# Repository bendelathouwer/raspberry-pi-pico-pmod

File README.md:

# raspberry-pi-pico-pmod
pico breakout with pmods

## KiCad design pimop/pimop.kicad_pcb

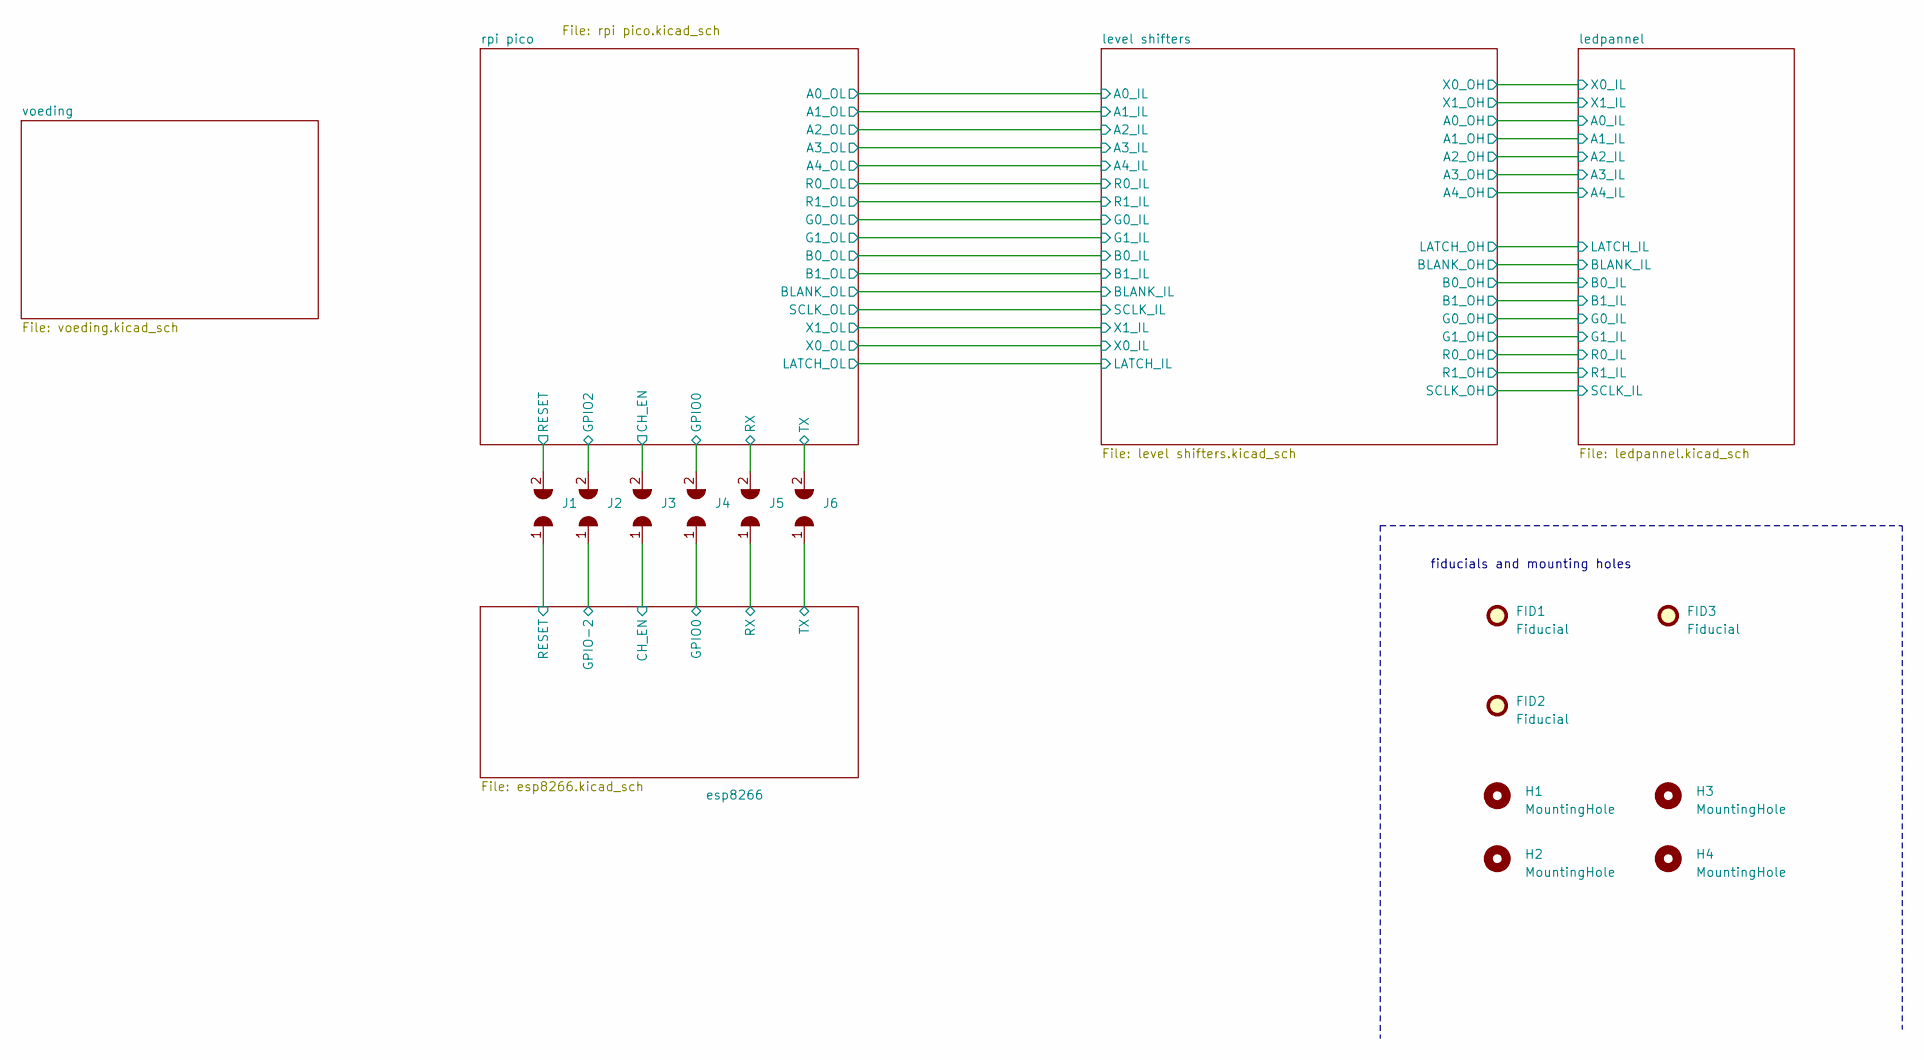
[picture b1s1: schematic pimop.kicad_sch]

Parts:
FID1, FID2, FID3: Fiducial; Fiducial_1.5mm_Mask4.5mm
H1, H2, H3, H4: MountingHole; MountingHole_2.2mm_M2_Pad
J1, J2, J3, J4, J5, J6: solderjumper_2pin; SolderJumper-2_P1.3mm_Open_Pad1.0x1.5mm

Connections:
/esp8266/CH_EN: J3.1; also elsewhere on the board
/esp8266/GPIO0: J4.1; also elsewhere on the board
/esp8266/GPIO-2: J2.1; also elsewhere on the board
/esp8266/RESET: J1.1; also elsewhere on the board
/esp8266/RX: J5.1; also elsewhere on the board
/esp8266/TX: J6.1; also elsewhere on the board
/rpi pico/GPIO16: J5.2; also elsewhere on the board
/rpi pico/GPIO17: J6.2; also elsewhere on the board
/rpi pico/GPIO18: J3.2; also elsewhere on the board
/rpi pico/GPIO19: J1.2; also elsewhere on the board
/rpi pico/GPIO20: J2.2; also elsewhere on the board
/rpi pico/GPIO21: J4.2; also elsewhere on the board

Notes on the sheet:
fiducials and mounting holes

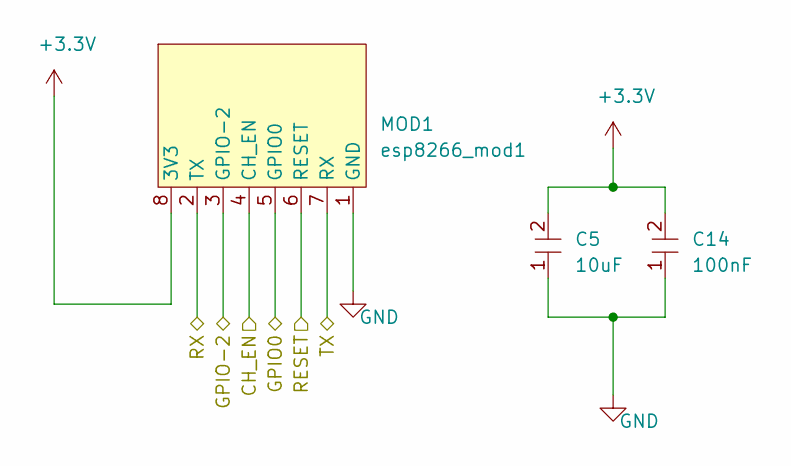
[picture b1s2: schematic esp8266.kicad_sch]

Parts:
C5: 10uF; 0603
C14: 100nF; 0603
MOD1: esp8266_mod1; esp8266mod

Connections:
+3V3: C5.2, C14.2, MOD1.8 (3V3); also elsewhere on the board
GND: C5.1, C14.1, MOD1.1 (GND); also elsewhere on the board

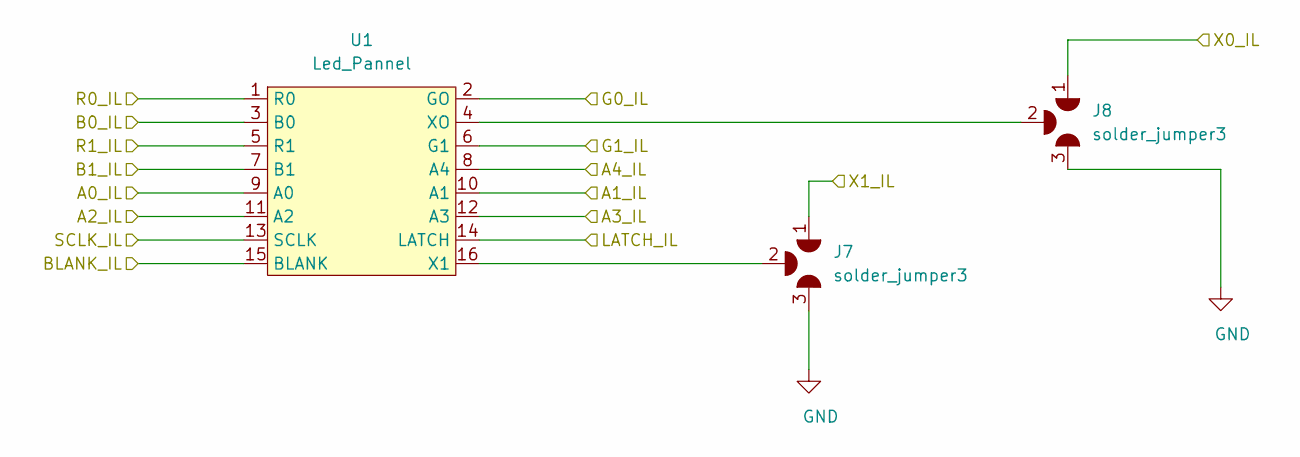
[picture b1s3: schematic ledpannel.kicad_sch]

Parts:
J7, J8: solder_jumper3; SolderJumper-3_P2.0mm_Open_TrianglePad1.0x1.5mm_NumberLabels
U1: Led_Pannel; 2x8

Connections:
/ledpannel/A0_IL: U1.9 (A0); also elsewhere on the board
/ledpannel/A1_IL: U1.10 (A1); also elsewhere on the board
/ledpannel/A2_IL: U1.11 (A2); also elsewhere on the board
/ledpannel/A3_IL: U1.12 (A3); also elsewhere on the board
/ledpannel/A4_IL: U1.8 (A4); also elsewhere on the board
/ledpannel/B0_IL: U1.3 (B0); also elsewhere on the board
/ledpannel/B1_IL: U1.7 (B1); also elsewhere on the board
/ledpannel/BLANK_IL: U1.15 (BLANK); also elsewhere on the board
/ledpannel/G0_IL: U1.2 (GO); also elsewhere on the board
/ledpannel/G1_IL: U1.6 (G1); also elsewhere on the board
/ledpannel/LATCH_IL: U1.14 (LATCH); also elsewhere on the board
/ledpannel/R0_IL: U1.1 (R0); also elsewhere on the board
/ledpannel/R1_IL: U1.5 (R1); also elsewhere on the board
/ledpannel/SCLK_IL: U1.13 (SCLK); also elsewhere on the board
/ledpannel/X0_IL: J8.1; also elsewhere on the board
/ledpannel/X1_IL: J7.1; also elsewhere on the board
GND: J7.3, J8.3; also elsewhere on the board
unnamed: J7.2, U1.16 (X1)
unnamed: J8.2, U1.4 (XO)

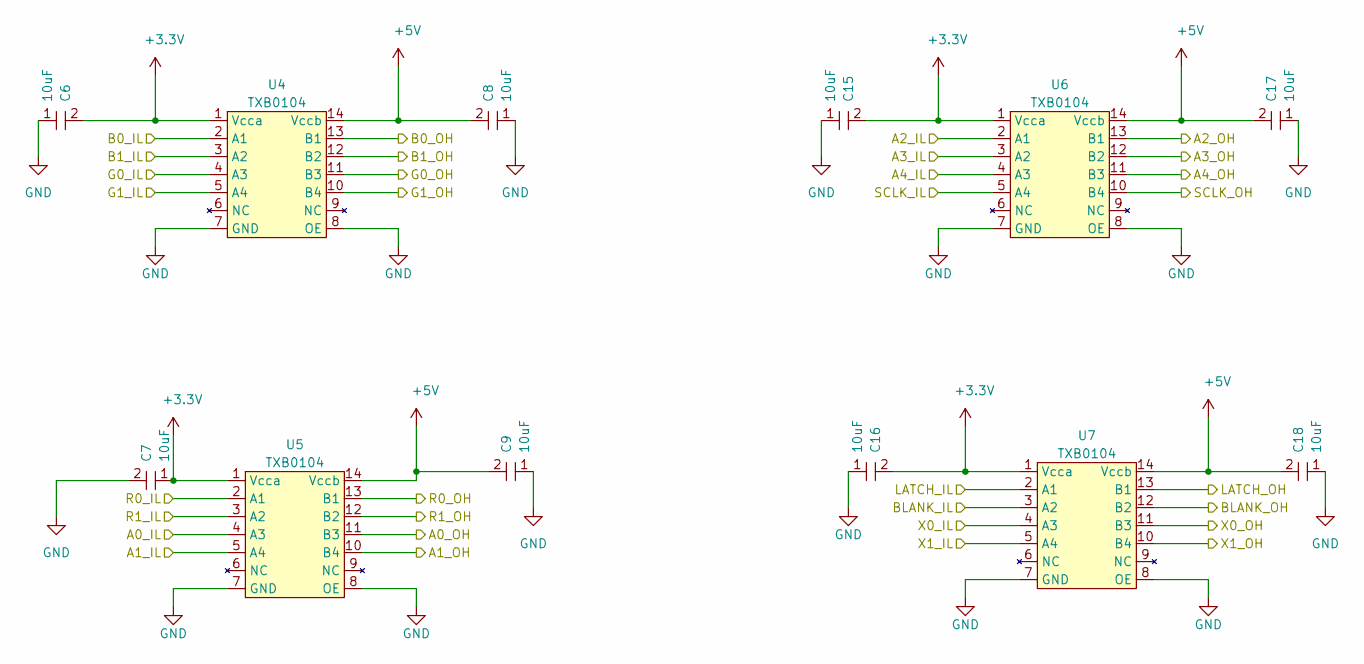
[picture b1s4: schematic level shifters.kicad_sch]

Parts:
C6, C7, C8, C9, C15, C16, C17, C18: 10uF; 0603
U4, U5, U6, U7: TXB0104; Texas_TXB0104PWR

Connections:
+3V3: C6.2, C7.1, C15.2, C16.2, U4.1 (Vcca), U5.1 (Vcca), U6.1 (Vcca), U7.1 (Vcca); also elsewhere on the board
/ledpannel/A0_IL: U5.11 (B3); also elsewhere on the board
/ledpannel/A1_IL: U5.10 (B4); also elsewhere on the board
/ledpannel/A2_IL: U6.13 (B1); also elsewhere on the board
/ledpannel/A3_IL: U6.12 (B2); also elsewhere on the board
/ledpannel/A4_IL: U6.11 (B3); also elsewhere on the board
/ledpannel/B0_IL: U4.13 (B1); also elsewhere on the board
/ledpannel/B1_IL: U4.12 (B2); also elsewhere on the board
/ledpannel/BLANK_IL: U7.12 (B2); also elsewhere on the board
/ledpannel/G0_IL: U4.11 (B3); also elsewhere on the board
/ledpannel/G1_IL: U4.10 (B4); also elsewhere on the board
/ledpannel/LATCH_IL: U7.13 (B1); also elsewhere on the board
/ledpannel/R0_IL: U5.13 (B1); also elsewhere on the board
/ledpannel/R1_IL: U5.12 (B2); also elsewhere on the board
/ledpannel/SCLK_IL: U6.10 (B4); also elsewhere on the board
/ledpannel/X0_IL: U7.11 (B3); also elsewhere on the board
/ledpannel/X1_IL: U7.10 (B4); also elsewhere on the board
/level shifters/A0_IL: U5.4 (A3); also elsewhere on the board
/level shifters/A1_IL: U5.5 (A4); also elsewhere on the board
/level shifters/A2_IL: U6.2 (A1); also elsewhere on the board
/level shifters/A3_IL: U6.3 (A2); also elsewhere on the board
/level shifters/A4_IL: U6.4 (A3); also elsewhere on the board
/level shifters/B0_IL: U4.2 (A1); also elsewhere on the board
/level shifters/B1_IL: U4.3 (A2); also elsewhere on the board
/level shifters/BLANK_IL: U7.3 (A2); also elsewhere on the board
/level shifters/R1_IL: U5.3 (A2); also elsewhere on the board
/level shifters/SCLK_IL: U6.5 (A4); also elsewhere on the board
/level shifters/X0_IL: U7.4 (A3); also elsewhere on the board
/level shifters/X1_IL: U7.5 (A4); also elsewhere on the board
/rpi pico/G0: U4.4 (A3); also elsewhere on the board
/rpi pico/G1: U4.5 (A4); also elsewhere on the board
/rpi pico/LATCH: U7.2 (A1); also elsewhere on the board
/rpi pico/R0: U5.2 (A1); also elsewhere on the board
GND: C6.1, C7.2, C8.1, C9.1, C15.1, C16.1, C17.1, C18.1, U4.7 (GND), U4.8 (OE), U5.7 (GND), U5.8 (OE), U6.7 (GND), U6.8 (OE), U7.7 (GND), U7.8 (OE); also elsewhere on the board

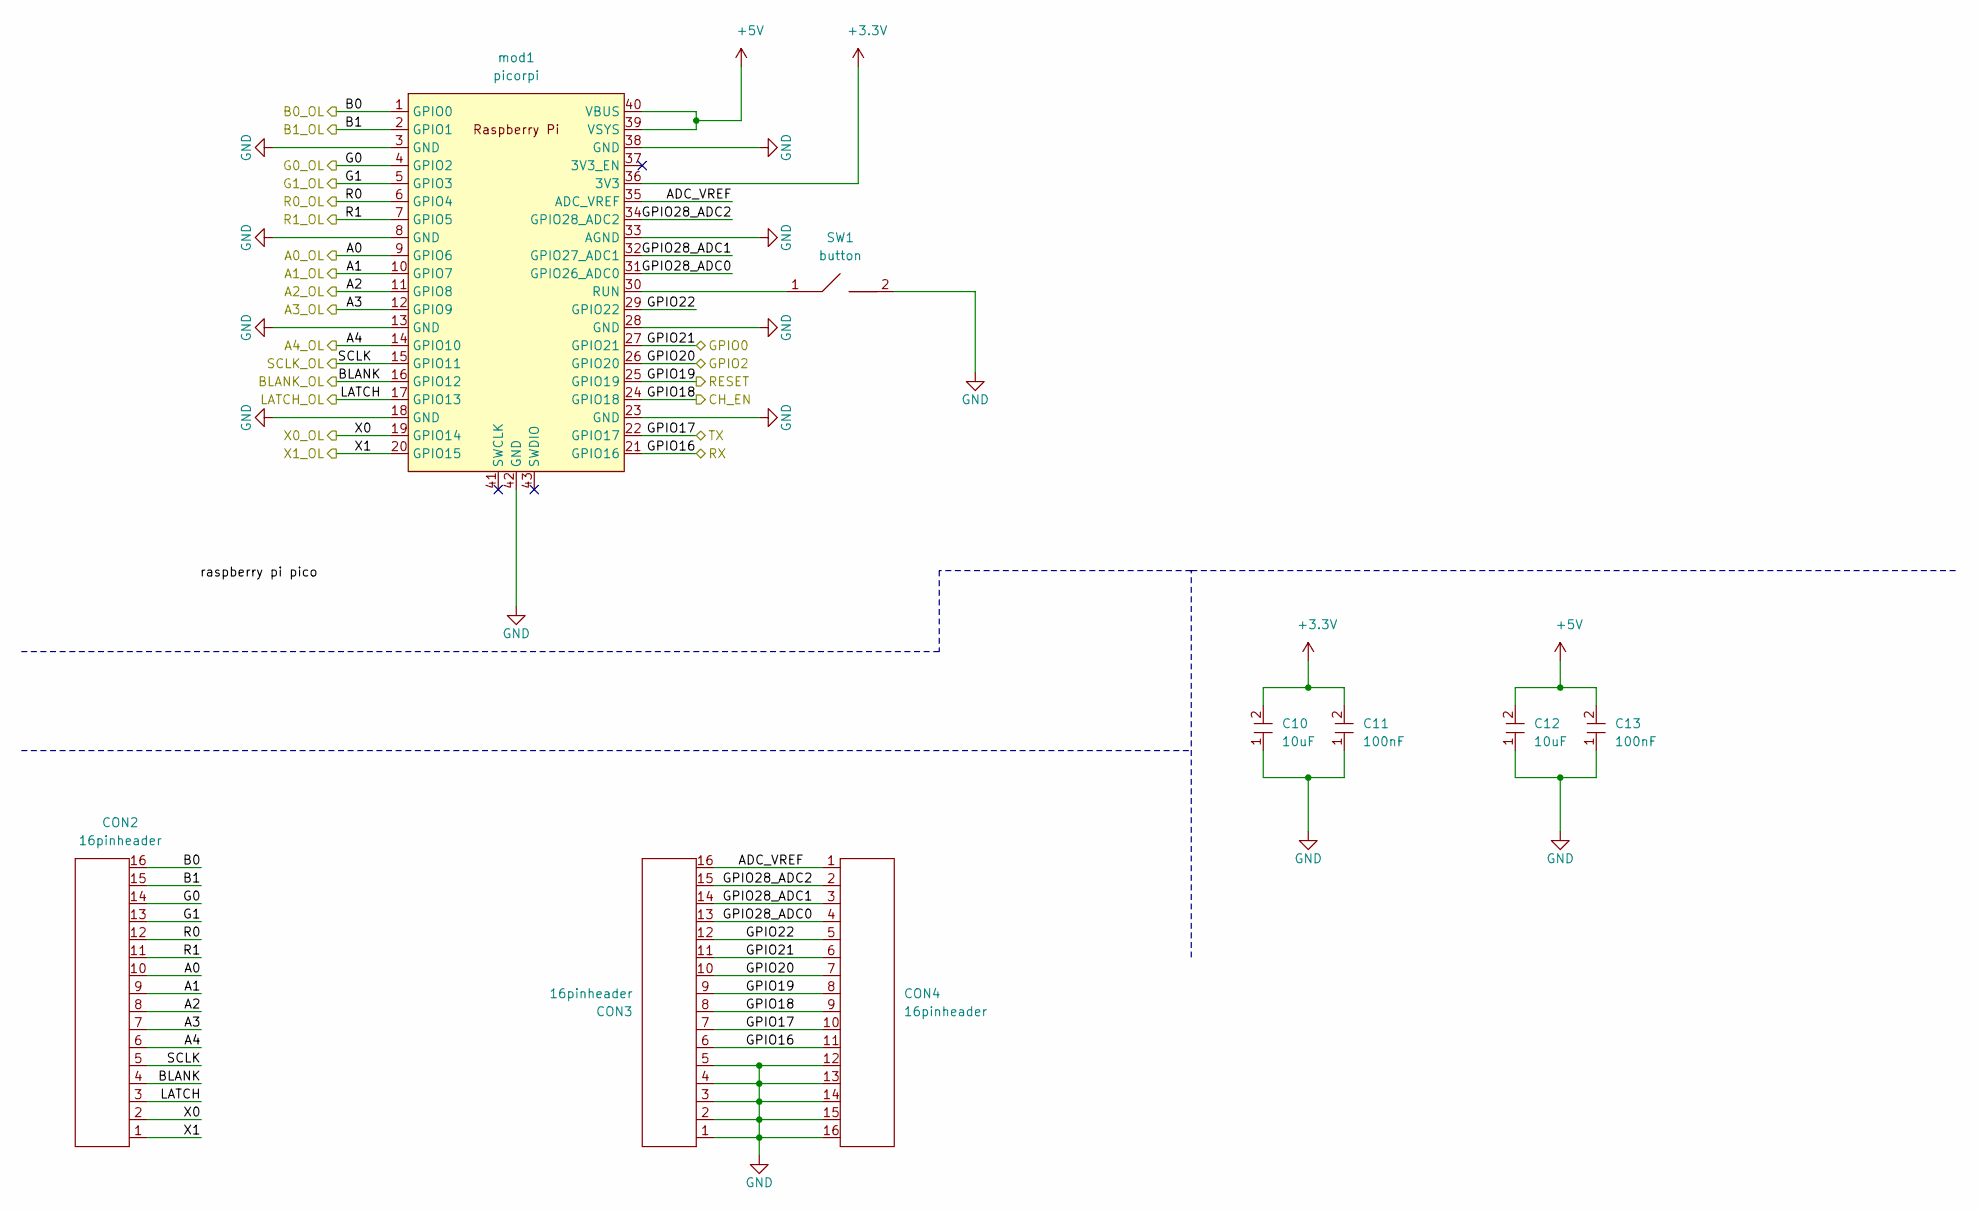
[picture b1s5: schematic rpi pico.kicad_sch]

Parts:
C10, C12: 10uF; 0603
C11, C13: 100nF; 0603
CON2, CON3, CON4: 16pinheader; 16 pin
SW1: button
mod1: picorpi; RPi_Pico_SMD_TH

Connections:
+3V3: C10.2, C11.2, mod1.36 (3V3); also elsewhere on the board
/level shifters/A0_IL: CON2.10, mod1.9 (GPIO6); also elsewhere on the board
/level shifters/A1_IL: CON2.9, mod1.10 (GPIO7); also elsewhere on the board
/level shifters/A2_IL: CON2.8, mod1.11 (GPIO8); also elsewhere on the board
/level shifters/A3_IL: CON2.7, mod1.12 (GPIO9); also elsewhere on the board
/level shifters/A4_IL: CON2.6, mod1.14 (GPIO10); also elsewhere on the board
/level shifters/B0_IL: CON2.16, mod1.1 (GPIO0); also elsewhere on the board
/level shifters/B1_IL: CON2.15, mod1.2 (GPIO1); also elsewhere on the board
/level shifters/BLANK_IL: CON2.4, mod1.16 (GPIO12); also elsewhere on the board
/level shifters/R1_IL: CON2.11, mod1.7 (GPIO5); also elsewhere on the board
/level shifters/SCLK_IL: CON2.5, mod1.15 (GPIO11); also elsewhere on the board
/level shifters/X0_IL: CON2.2, mod1.19 (GPIO14); also elsewhere on the board
/level shifters/X1_IL: CON2.1, mod1.20 (GPIO15); also elsewhere on the board
/rpi pico/ADC_VREF: CON3.16, CON4.1, mod1.35 (ADC_VREF)
/rpi pico/G0: CON2.14, mod1.4 (GPIO2); also elsewhere on the board
/rpi pico/G1: CON2.13, mod1.5 (GPIO3); also elsewhere on the board
/rpi pico/GPIO16: CON3.6, CON4.11, mod1.21 (GPIO16); also elsewhere on the board
/rpi pico/GPIO17: CON3.7, CON4.10, mod1.22 (GPIO17); also elsewhere on the board
/rpi pico/GPIO18: CON3.8, CON4.9, mod1.24 (GPIO18); also elsewhere on the board
/rpi pico/GPIO19: CON3.9, CON4.8, mod1.25 (GPIO19); also elsewhere on the board
/rpi pico/GPIO20: CON3.10, CON4.7, mod1.26 (GPIO20); also elsewhere on the board
/rpi pico/GPIO21: CON3.11, CON4.6, mod1.27 (GPIO21); also elsewhere on the board
/rpi pico/GPIO22: CON3.12, CON4.5, mod1.29 (GPIO22)
/rpi pico/GPIO26_ADC0: CON3.13, CON4.4, mod1.31 (GPIO26_ADC0)
/rpi pico/GPIO27_ADC1: CON3.14, CON4.3, mod1.32 (GPIO27_ADC1)
/rpi pico/GPIO28_ADC2: CON3.15, CON4.2, mod1.34 (GPIO28_ADC2)
/rpi pico/LATCH: CON2.3, mod1.17 (GPIO13); also elsewhere on the board
/rpi pico/R0: CON2.12, mod1.6 (GPIO4); also elsewhere on the board
GND: C10.1, C11.1, C12.1, C13.1, CON3.1, CON3.2, CON3.3, CON3.4, CON3.5, CON4.12, CON4.13, CON4.14, CON4.15, CON4.16, SW1.2, mod1.3 (GND), mod1.8 (GND), mod1.13 (GND), mod1.18 (GND), mod1.23 (GND), mod1.28 (GND), mod1.33 (AGND), mod1.38 (GND), mod1.42 (GND); also elsewhere on the board
unnamed: SW1.1, mod1.30 (RUN)

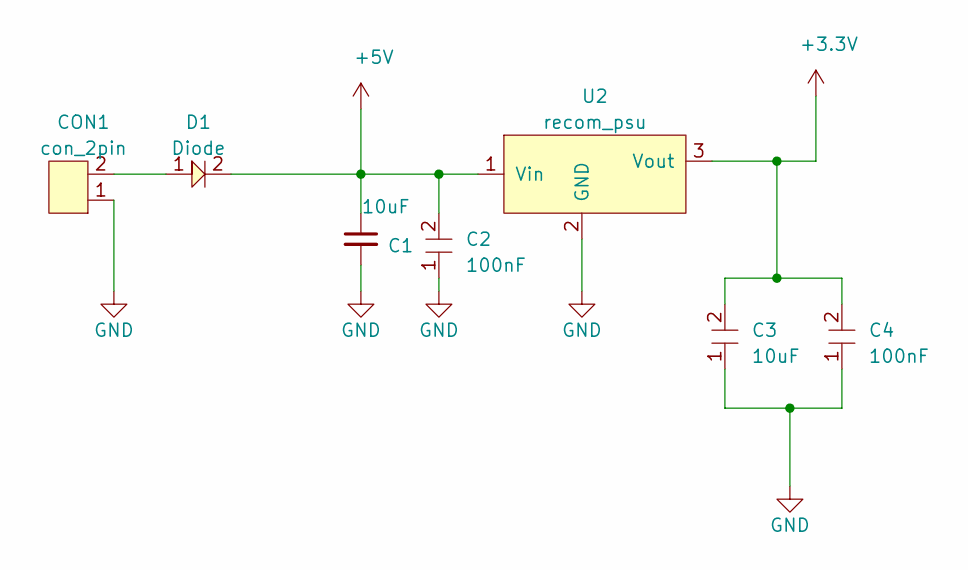
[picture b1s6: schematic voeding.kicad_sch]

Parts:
C1, C3: 10uF; 0603
C2, C4: 100nF; 0603
CON1: con_2pin; 2pin_screw_vast
D1: Diode; DO214
U2: recom_psu; recom psu

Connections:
+3V3: C3.2, C4.2, U2.3 (Vout); also elsewhere on the board
GND: C1.2, C2.1, C3.1, C4.1, CON1.1, U2.2 (GND); also elsewhere on the board
unnamed: CON1.2, D1.1

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
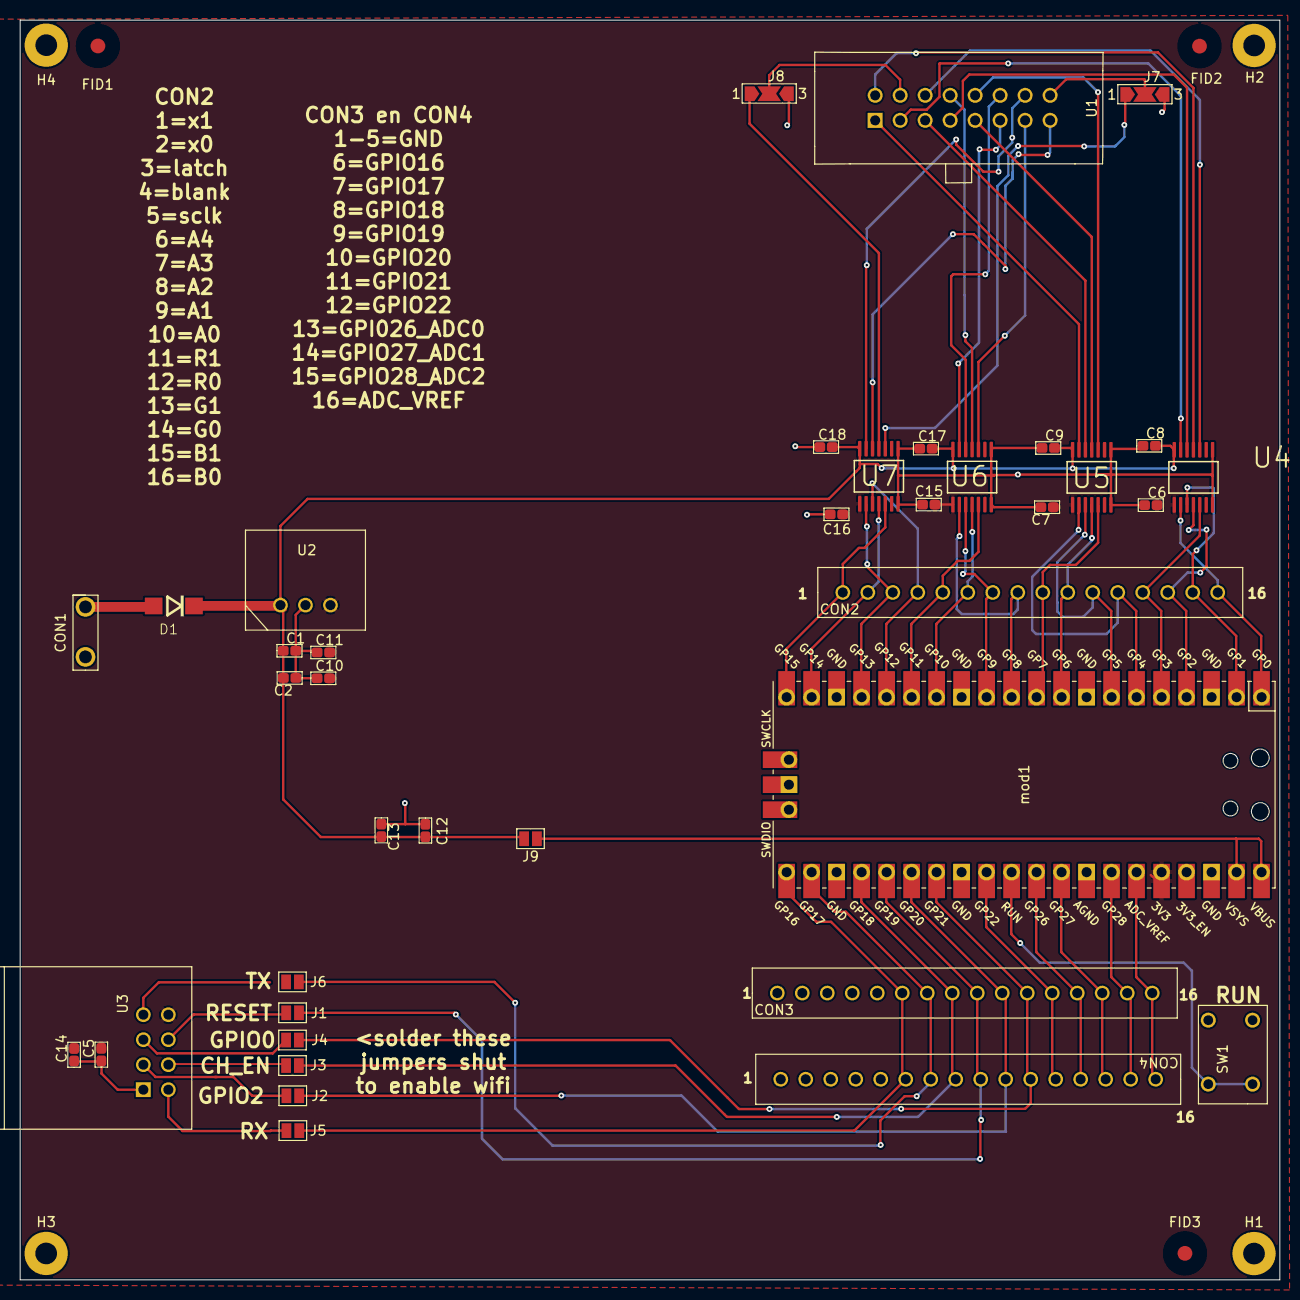
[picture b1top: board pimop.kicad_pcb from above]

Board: 2 copper layers, 128.0 x 128.0 mm, 46 parts (0 on the bottom side), 57 nets.

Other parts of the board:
J9: solderjumper_2pin; SolderJumper-2_P1.3mm_Open_Pad1.0x1.5mm
U3: esp8266_mod1; esp8266mod

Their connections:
+3V3: U3.8 (3V3); also elsewhere on the board
/esp8266/CH_EN: U3.4 (CH_EN); also elsewhere on the board
/esp8266/GPIO0: U3.5 (GPIO0); also elsewhere on the board
/esp8266/GPIO-2: U3.3 (GPIO-2); also elsewhere on the board
/esp8266/RESET: U3.6 (RESET); also elsewhere on the board
/esp8266/RX: U3.2 (TX); also elsewhere on the board
/esp8266/TX: U3.7 (RX); also elsewhere on the board
GND: U3.1 (GND); also elsewhere on the board

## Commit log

2021-03-04 schema
    schema bijna afgewerkt
2021-03-09 schema afgewerkt
    schema afgewerkt
2021-05-18 e5yt
    45y
